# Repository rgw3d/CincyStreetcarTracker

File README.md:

# Cincinnati Streetcar Tracker

I learned that the real-time transit information for the Cincinnati Streetcar was published by Metro here: https://www.go-metro.com/about/developer-data/ in [GTFS](https://en.wikipedia.org/wiki/GTFS) form. 

And then I saw https://www.traintrackr.io/ and was inspired to make a version for Cincinnati.

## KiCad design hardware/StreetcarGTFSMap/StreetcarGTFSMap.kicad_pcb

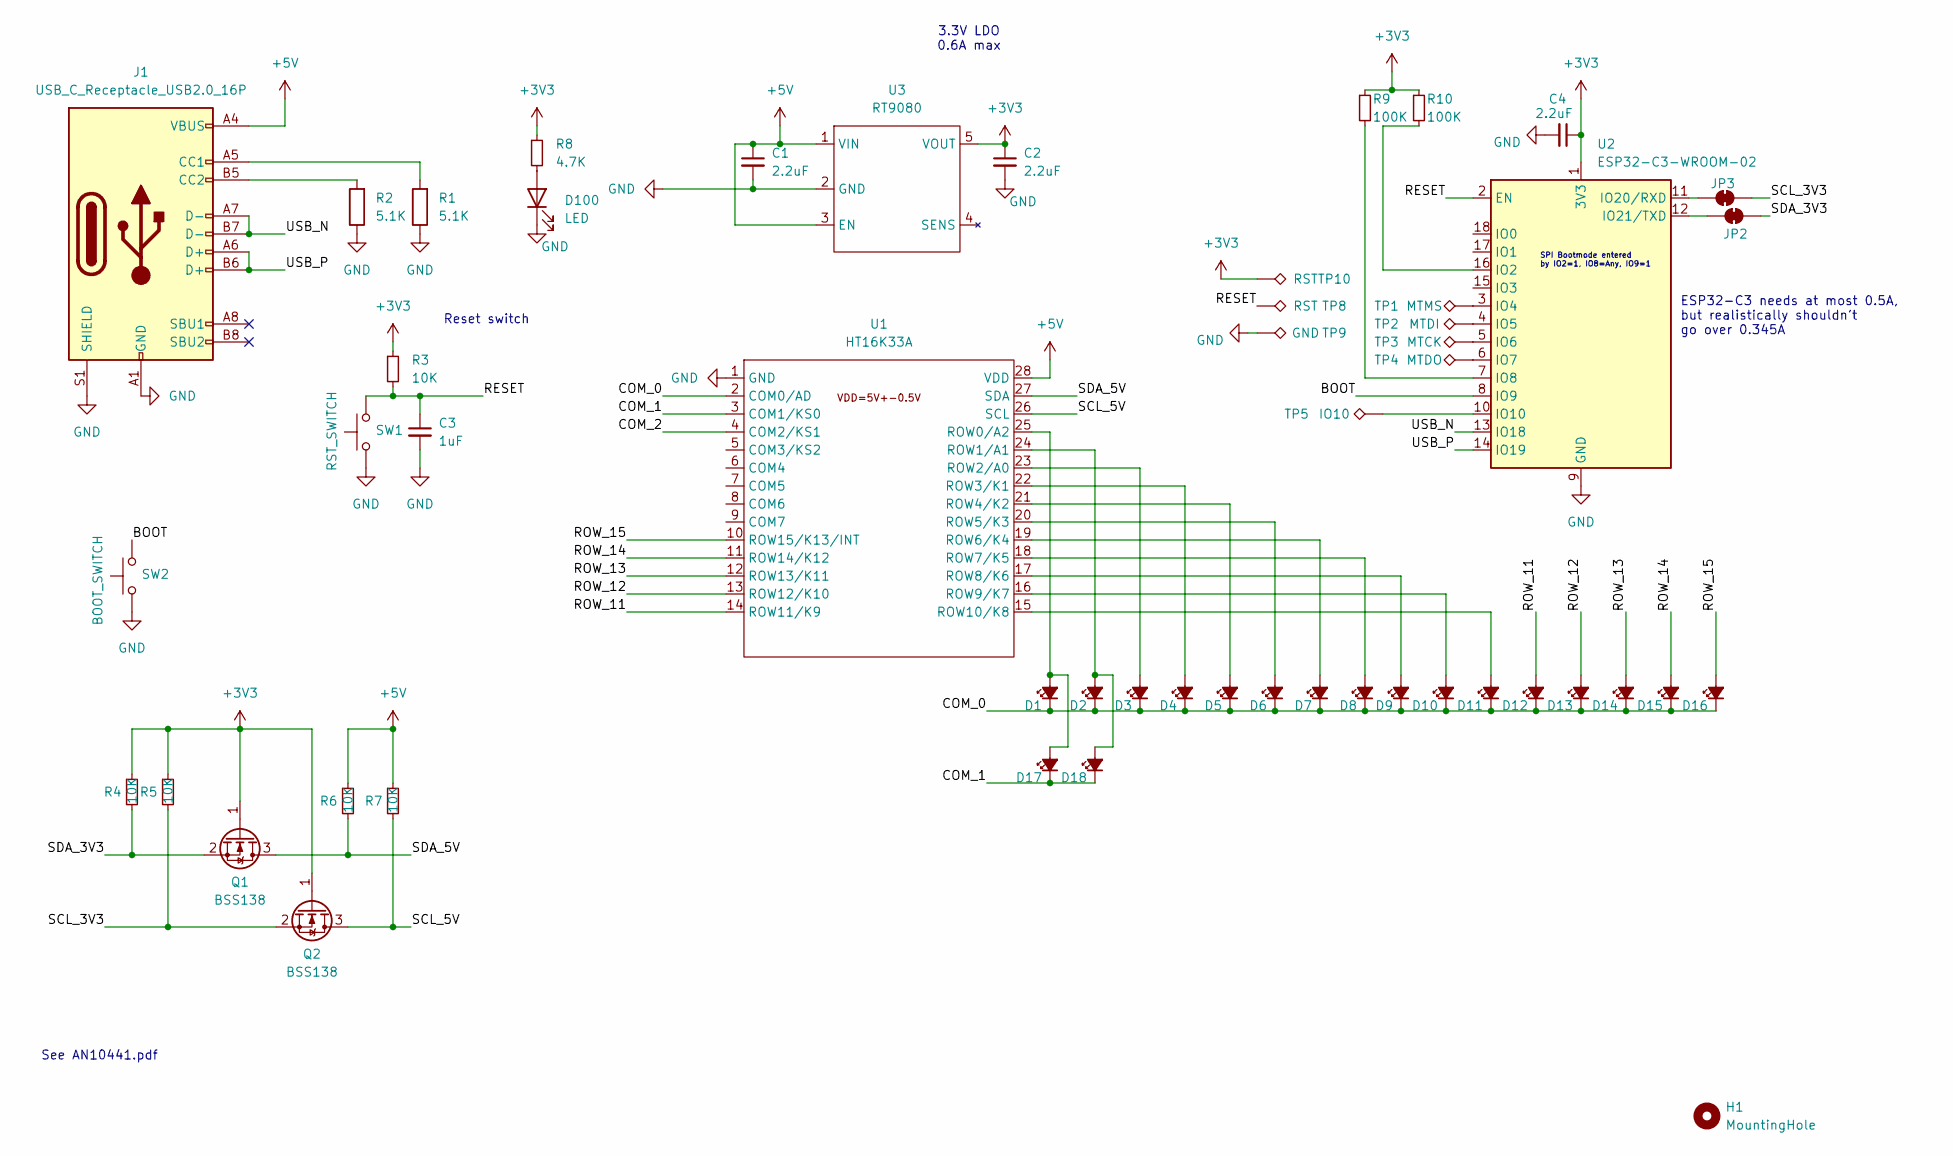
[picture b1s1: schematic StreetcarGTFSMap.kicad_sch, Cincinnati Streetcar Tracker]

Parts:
C1, C2, C4: 2.2uF; C_0603_1608Metric_Pad1.08x0.95mm_HandSolder
C3: 1uF; C_0603_1608Metric_Pad1.08x0.95mm_HandSolder
D1, D2, D3, D4, D5, D6, D7, D8, D9, D10, D11, D12, D13, D14, D15, D16, D17, D18: LED_Small_Filled; LED_0603_1608Metric_Pad1.05x0.95mm_HandSolder
D100: LED; LED_0603_1608Metric_Pad1.05x0.95mm_HandSolder
H1: MountingHole; MountingHole_2.1mm
J1: USB_C_Receptacle_USB2.0_16P; USB_C_Receptacle_GCT_USB4105-xx-A_16P_TopMnt_Horizontal
JP2, JP3: SolderJumper_2_Bridged; SolderJumper-2_P1.3mm_Bridged_Pad1.0x1.5mm
Q1, Q2: BSS138; SOT-23_Handsoldering
R1, R2: 5.1K; R_0603_1608Metric_Pad0.98x0.95mm_HandSolder
R3, R4, R5, R6, R7: 10K; R_0603_1608Metric_Pad0.98x0.95mm_HandSolder
R8: 4.7K; R_0603_1608Metric_Pad0.98x0.95mm_HandSolder
R9, R10: 100K; R_0603_1608Metric_Pad0.98x0.95mm_HandSolder
SW1: RST_SWITCH; SW_SPST_PTS647_Sx50
SW2: BOOT_SWITCH; SW_SPST_PTS647_Sx50
TP1: MTMS; TestPoint_Pad_2.5x2.5mm
TP2: MTDI; TestPoint_Pad_2.5x2.5mm
TP3: MTCK; TestPoint_Pad_2.5x2.5mm
TP4: MTDO; TestPoint_Pad_2.5x2.5mm
TP5: IO10; TestPoint_Pad_2.5x2.5mm
TP8, TP10: RST; TestPoint_Pad_2.5x2.5mm
TP9: GND; TestPoint_Pad_2.5x2.5mm
U1: HT16K33A; SOP-28_8.4x18.16mm_P1.27mm
U2: ESP32-C3-WROOM-02
U3: RT9080; TSOT-23-5

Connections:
+3V3: C2.1, C4.1, Q1.1 (G), Q2.1 (G), R3.1, R4.1, R5.1, R8.1, R9.1, R10.1, TP10.1, U2.1 (3V3), U3.5 (VOUT)
+5V: C1.1, J1.A4 (VBUS), J1.A9 (VBUS), J1.B4 (VBUS), J1.B9 (VBUS), R6.1, R7.1, U1.28 (VDD), U3.1 (VIN), U3.3 (EN)
/BOOT: SW2.2, U2.8 (IO9)
/COM_0: D1.1 (K), D2.1 (K), D3.1 (K), D4.1 (K), D5.1 (K), D6.1 (K), D7.1 (K), D8.1 (K), D9.1 (K), D10.1 (K), D11.1 (K), D12.1 (K), D13.1 (K), D14.1 (K), D15.1 (K), D16.1 (K), U1.2 (COM0/AD)
/COM_1: D17.1 (K), D18.1 (K), U1.3 (COM1/KS0)
/COM_2: U1.4 (COM2/KS1)
/RESET: C3.1, R3.2, SW1.2, TP8.1, U2.2 (EN)
/ROW_11: D12.2 (A), U1.14 (ROW11/K9)
/ROW_12: D13.2 (A), U1.13 (ROW12/K10)
/ROW_13: D14.2 (A), U1.12 (ROW13/K11)
/ROW_14: D15.2 (A), U1.11 (ROW14/K12)
/ROW_15: D16.2 (A), U1.10 (ROW15/K13/INT)
/SCL_3V3: JP3.2 (B), Q2.2 (S), R5.2
/SCL_5V: Q2.3 (D), R7.2, U1.26 (SCL)
/SDA_3V3: JP2.2 (B), Q1.2 (S), R4.2
/SDA_5V: Q1.3 (D), R6.2, U1.27 (SDA)
/USB_N: J1.A7 (D-), J1.B7 (D-), U2.13 (IO18)
/USB_P: J1.A6 (D+), J1.B6 (D+), U2.14 (IO19)
GND: C1.2, C2.2, C3.2, C4.2, D100.1 (K), J1.A1 (GND), J1.A12 (GND), J1.B1 (GND), J1.B12 (GND), J1.S1 (SHIELD), R1.1, R2.1, SW1.1, SW2.1, TP9.1, U1.1 (GND), U2.9 (GND), U2.19 (GND), U3.2 (GND)
unnamed: D1.2 (A), D17.2 (A), U1.25 (ROW0/A2)
unnamed: D3.2 (A), U1.23 (ROW2/A0)
unnamed: D4.2 (A), U1.22 (ROW3/K1)
unnamed: D5.2 (A), U1.21 (ROW4/K2)
unnamed: D6.2 (A), U1.20 (ROW5/K3)
unnamed: D7.2 (A), U1.19 (ROW6/K4)
unnamed: D8.2 (A), U1.18 (ROW7/K5)
unnamed: D9.2 (A), U1.17 (ROW8/K6)
unnamed: D10.2 (A), U1.16 (ROW9/K7)
unnamed: D11.2 (A), U1.15 (ROW10/K8)
unnamed: D2.2 (A), D18.2 (A), U1.24 (ROW1/A1)
unnamed: D100.2 (A), R8.2
unnamed: J1.A5 (CC1), R1.2
unnamed: J1.B5 (CC2), R2.2
unnamed: JP2.1 (A), U2.12 (IO21/TXD)
unnamed: JP3.1 (A), U2.11 (IO20/RXD)
unnamed: R10.2, U2.16 (IO2)
unnamed: TP1.1, U2.3 (IO4)
unnamed: TP2.1, U2.4 (IO5)
unnamed: TP3.1, U2.5 (IO6)
unnamed: TP4.1, U2.6 (IO7)
unnamed: R9.2, U2.7 (IO8)
unnamed: TP5.1, U2.10 (IO10)

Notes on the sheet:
Reset switch
3.3V LDO 0.6A max
ESP32-C3 needs at most 0.5A, but realistically shouldn't go over 0.345A
See AN10441.pdf
SPI Bootmode entered by IO2=1, IO8=Any, IO9=1

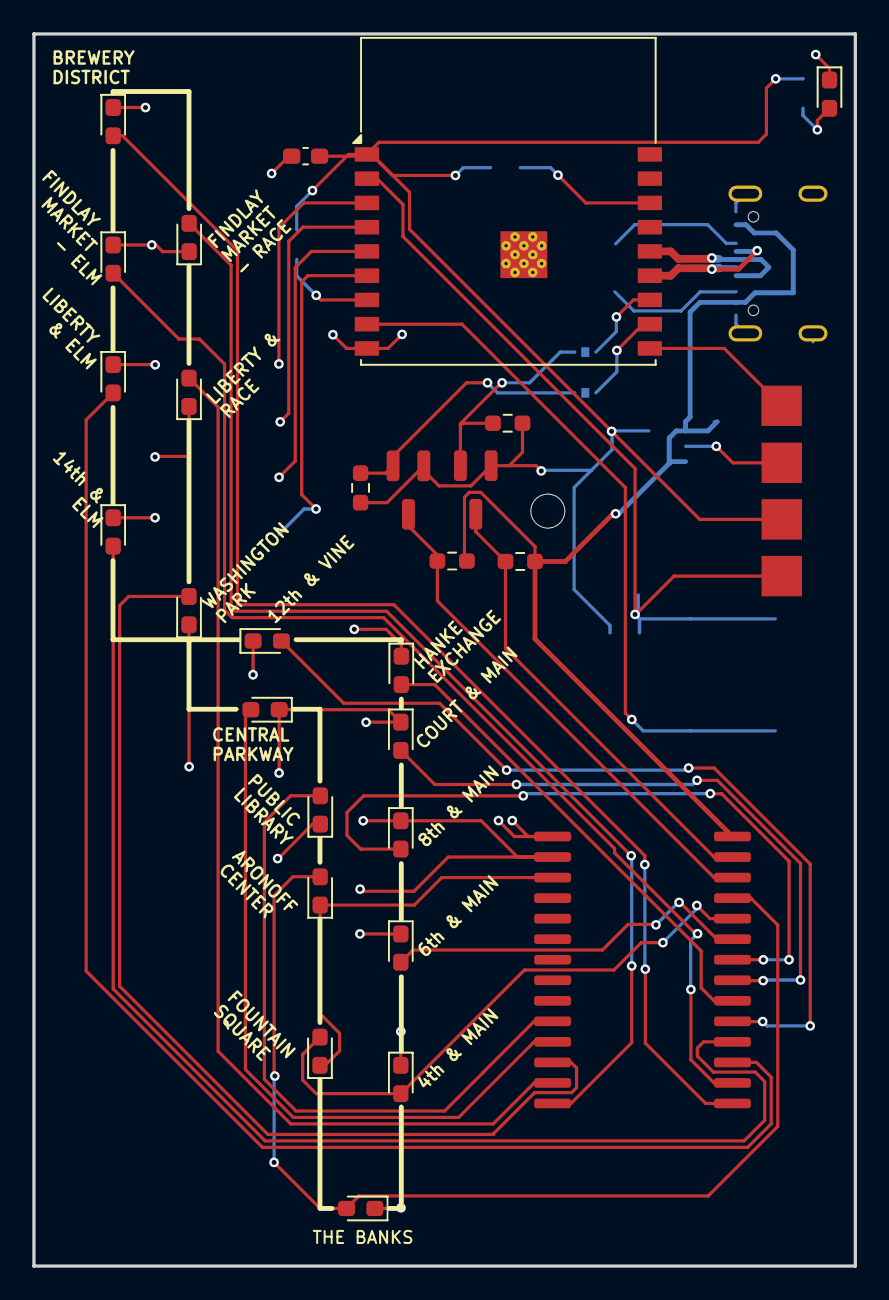
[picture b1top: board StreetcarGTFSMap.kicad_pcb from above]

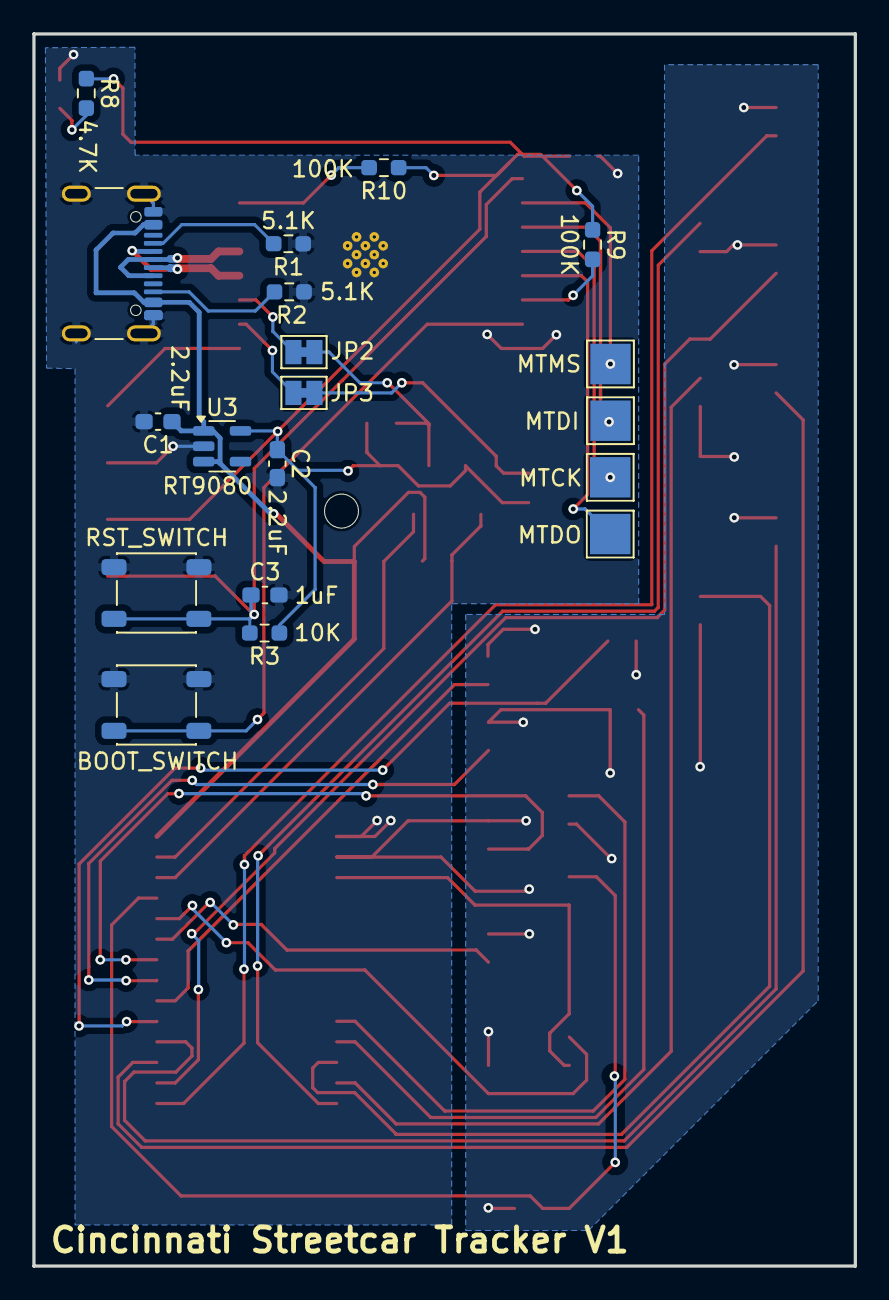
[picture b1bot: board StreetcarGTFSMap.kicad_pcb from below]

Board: 2 copper layers, 50.8 x 76.2 mm, 52 parts (19 on the bottom side), 41 nets.
